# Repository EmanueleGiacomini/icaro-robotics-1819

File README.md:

# [18-19] Icaro Robotics
Repository for ICARO Project 2018-2019 for Pacinotti students

## Struttura della repository
    .
    ├── elettronica
    │   ├── CAM_settings
    |   ├── design_rule_check
    |   ├── eagle_lib
    |   └── rescue
    |       ├── IcaroRescue_Sol
    |       └── IcaroRescue_TODO
    └── informatica
        └── rescue
            ├── link_utili
            |   └── Icaro 2018-2019.txt
            └── rescue_firmware

La struttura reale contiene molti più file che però non sono molto rilevanti per te.

## Informatica
### Cosa devi fare:
Se sei l'informatico del tuo gruppo, segui questi passi per recuperare il programma su cui lavorare:
1. Scarica il repository tramite il tastone verde **Clone or download** in alto nella pagina
2. Decomprimi il file .zip che hai scaricato, possibilmente dentro una cartella facilmente accessibile
3. Ti consiglio di creare un tuo repository (TODO: Guida per repository) e copiarci dentro la cartella **rescue_firmware** presente nella cartella __informatica/rescue/__. Alternativamente puoi lavorare direttamente all'interno della cartella decompressa.

### Primi passi :)
Il tuo primo obiettivo è quello di far muovere il robot... come facciamo ?
All'interno della cartella __rescue_firmware__ sono presenti questi files

      rescue_firmware/
      ├── rescue_drive.cpp
      ├── rescue_drive.h
      ├── rescue_firmware.ino
      ├── rescue_motore.cpp
      └── rescue_motore.h

Come puoi notare, (apparte rescue_firmware.ino) tutti i file hanno un corrispettivo **.h** e un **.cpp**. Questo perché
in C++ la costruzione di una libreria è suddivisa in due programmi complementari contenuti in questi due files.

Senza allungare troppo la brodaglia, ti ho semplificato il lavoro costruendo uno scheletro di tutti i programmi.
Per far muovere il robot dovrai completare prima rescue_motore **.cpp** seguendo le istruzioni fornite (leggiti anche rescue_motore **.h** in quanto contiene le definizioni delle strutture e delle variabili usate)

Come fai a verificare se il programma funziona ? 
Qui entra in gioco il programma **rescue_firmware.ino** che puoi aprire con __Arduino IDE__. Una volta aperto,
premi la freccia in alto per verificare il programma (oppure premi Ctrl-R) e il compilatore ti dirà se ci sono errori (oppure orrori) di programmazione nei file che hai scritto.

Quando hai terminato di scrivere il programma, puoi caricare il programma su Arduino (TODO) e il robot si muoverà formando un quadrato :)

### Rilevazione degli ostacoli
// TODO

### Seguiamo la linea !
// TODO

### Quasi fatto !
// TODO
##
## Elettronica
### Libreria Icaro (icaro.lbr)
La libreria __icaro.lbr__ contiene i componenti realizzati da voi in questi anni.
Attualmente la libreria contiene:
* __GY31 TCS230__ (Sensore di colore)

### Design Rule Check (DRU)
Il file __Sparkfun.dru__ contiene le regole di design necessarie ad Eagle per testare il tuo circuito, ed assicurarti che non abbia fatto orrori durante la creazione del board.
Per attivarlo segui i seguenti passi:
1) Apri il file .brd del tuo circuito
2) Scegli lo strumento DRC
3) Premi sul tasto __Load...__ e carica il file __Sparkfun.dru__
4) Clicca su __Check__ e osserva gli errori che ti stampa. Il tuo obiettivo è __rimuovere tutti gli errori__

### Rescue Line Sensor
La cartella rescue/__IcaroRescue_TODO/__ contiene alcuni progetti pre completati di sensori di linea. Questo per semplificarti il lavoro di stesura dei componenti visti a lezione (e per evitare a me giorni di debug a capire che orrori hai fatto!).
Il tuo compito è scegliere uno di questi circuiti, completarne la pcb e poi contattarmi per la verifica del circuito... Buon lavoro!

## Reference

__TCS230__ Color Sensor:
1) [HowToMechatronics guide](https://howtomechatronics.com/tutorials/arduino/arduino-color-sensing-tutorial-tcs230-tcs3200-color-sensor/)

2) [TCS230 Sensor Calibration](https://arduinoplusplus.wordpress.com/2015/07/15/tcs230tcs3200-sensor-calibration/)

3) [RGB to HSL](https://www.programmingalgorithms.com/algorithm/rgb-to-hsl?lang=C)

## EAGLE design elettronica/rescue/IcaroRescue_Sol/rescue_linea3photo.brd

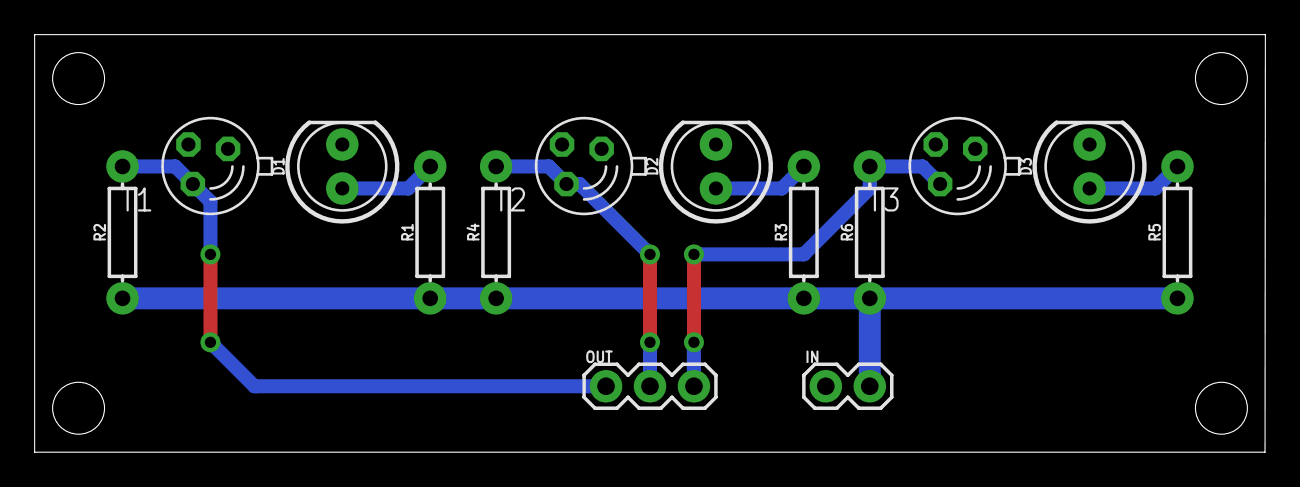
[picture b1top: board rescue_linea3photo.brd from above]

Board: 2 copper layers, 71.1 x 24.1 mm, 14 parts (0 on the bottom side), 8 nets.

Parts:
D1, D2, D3: LED_5MM
IN: 1X02
OUT: 455-1750-1-ND; 1X03
R1, R3, R5: 220; AXIAL-0.3
R2, R4, R6: 10k; AXIAL-0.3
T1, T2, T3: BP103

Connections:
GND: D1.K, D2.K, D3.K, IN.1, T1.E, T2.E, T3.E
unnamed: D2.A, R3.P$2
unnamed: D3.A, R5.P$2
unnamed: D1.A, R1.P$2
OUT1: OUT.1, R2.P$2, T1.C
OUT2: OUT.2, R4.P$2, T2.C
OUT3: OUT.3, R6.P$2, T3.C
VCC: IN.2, R1.P$1, R2.P$1, R3.P$1, R4.P$1, R5.P$1, R6.P$1

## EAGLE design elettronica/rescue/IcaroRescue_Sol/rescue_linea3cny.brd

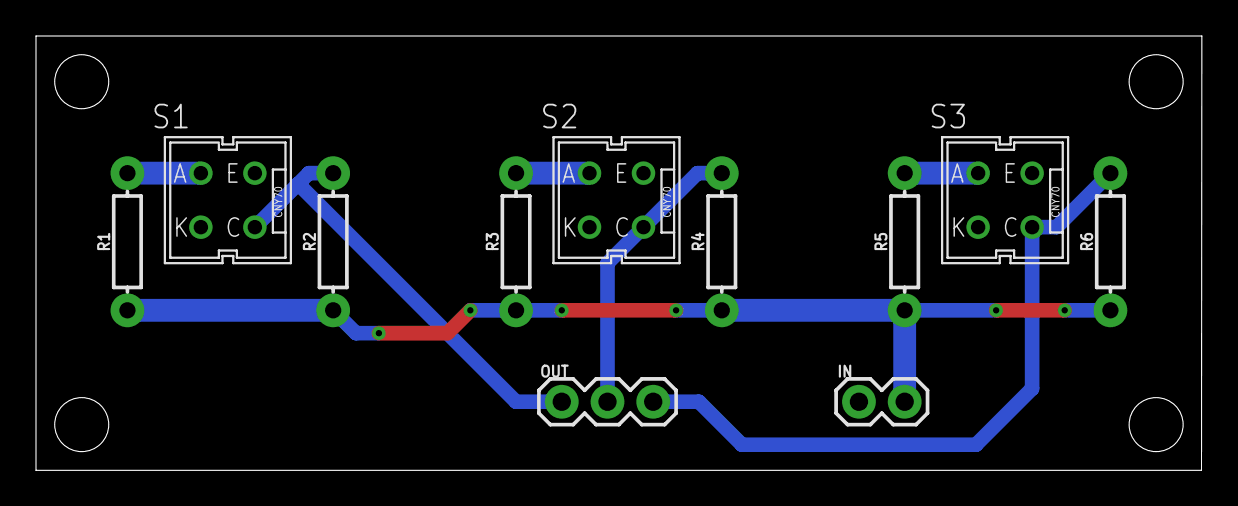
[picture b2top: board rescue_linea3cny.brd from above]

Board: 2 copper layers, 64.8 x 24.1 mm, 11 parts (0 on the bottom side), 8 nets.

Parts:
IN: 1X02
OUT: 455-1750-1-ND; 1X03
R1, R3, R5: 220; AXIAL-0.3
R2, R4, R6: 10k; AXIAL-0.3
S1, S2, S3: CNY70

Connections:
GND: IN.1, S1.E, S1.K, S2.E, S2.K, S3.E, S3.K
unnamed: R3.P$2, S2.A
unnamed: R1.P$2, S1.A
unnamed: R5.P$2, S3.A
OUT1: OUT.1, R2.P$2, S1.C
OUT2: OUT.2, R4.P$2, S2.C
OUT3: OUT.3, R6.P$2, S3.C
VCC: IN.2, R1.P$1, R2.P$1, R3.P$1, R4.P$1, R5.P$1, R6.P$1

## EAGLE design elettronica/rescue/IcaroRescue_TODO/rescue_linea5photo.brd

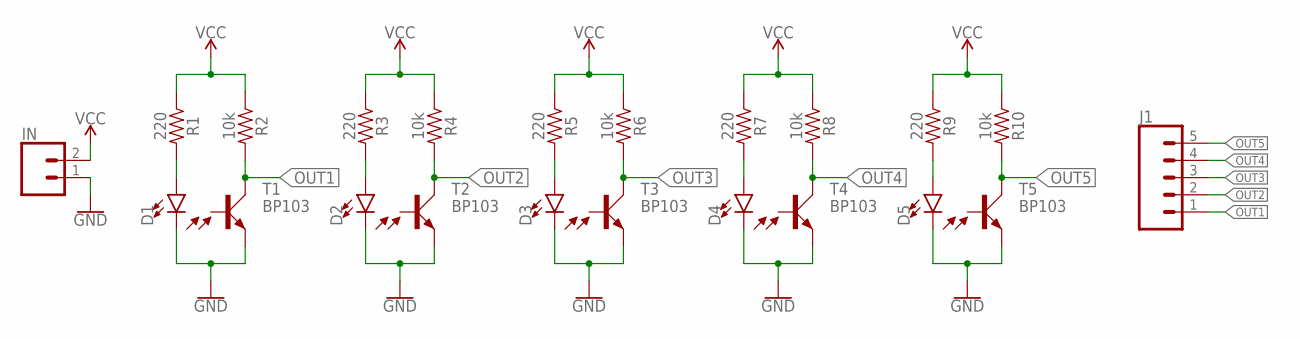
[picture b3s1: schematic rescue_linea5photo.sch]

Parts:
D1, D2, D3, D4, D5: LED5MM; LED_5MM
IN: CONN_02; 1X02
J1: CONN_05; 1X05
R1, R3, R5, R7, R9: 220; AXIAL-0.3
R2, R4, R6, R8, R10: 10k; AXIAL-0.3
T1, T2, T3, T4, T5: BP103

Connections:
GND: D1.K (C), D2.K (C), D3.K (C), D4.K (C), D5.K (C), IN.1, T1.E, T2.E, T3.E, T4.E, T5.E
unnamed: D2.A, R3.P$2 (2)
unnamed: D3.A, R5.P$2 (2)
unnamed: D4.A, R7.P$2 (2)
unnamed: D1.A, R1.P$2 (2)
unnamed: D5.A, R9.P$2 (2)
OUT1: J1.1, R2.P$2 (2), T1.C
OUT2: J1.2, R4.P$2 (2), T2.C
OUT3: J1.3, R6.P$2 (2), T3.C
OUT4: J1.4, R8.P$2 (2), T4.C
OUT5: J1.5, R10.P$2 (2), T5.C
VCC: IN.2, R1.P$1 (1), R2.P$1 (1), R3.P$1 (1), R4.P$1 (1), R5.P$1 (1), R6.P$1 (1), R7.P$1 (1), R8.P$1 (1), R9.P$1 (1), R10.P$1 (1)

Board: 2 copper layers, 22 parts (0 on the bottom side), 12 nets, no tracks yet.

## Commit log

2018-04-10 Inserito esempio controllo-flag
2018-04-16 Aggiunto firmware autocalibrazione
2018-04-17 Aggiunto file pianificazione
2018-11-10 Added rescue files
2018-11-10 But wait ! there's more !
2018-11-10 completato funzioni del rescue
2018-11-12 librerie per pixy
2018-11-15 link_utili
2018-11-22 tutto pixy
2018-12-10 Update: rescue_linefollower, rescsue_joints
2018-12-12 Added colorsensor lib, updated bumper
2018-12-13 Add line sensor electronics
2018-12-13 Added line sensor electronics
2018-12-24 Updated rescue firmware
2019-02-05 Add pid, rescue_linea, rescue_linea_internal
2019-03-17 add eeprom

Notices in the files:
parts and their libraries:
SparkFun-Connectors: Licensing: Creative Commons ShareAlike 4.0 International - https://creativecommons.org/licenses/by-sa/4.0
